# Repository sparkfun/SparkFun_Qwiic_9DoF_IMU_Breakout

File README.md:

SparkFun Qwiic 9DoF IMU  Breakout
========================================

[*SparkFun Qwiic 9DoF IMU  Breakout (15335)*](https://www.sparkfun.com/products/15335)

The SparkFun 9DoF IMU Breakout incorporates all the amazing features of Invensense's ICM-20948 into a Qwiic-enabled breakout board complete with a logic shifter and broken out GPIO pins for all your motion sensing needs. The ICM-20948 itself is an extremely low powered, I2C and SPI enabled 9-axis motion tracking device that is ideally suited for smartphones, tablets, wearable sensors, and IoT applications. Utilizing our handy Qwiic system, no soldering is required to connect it to the rest of your system. However, we still have broken out 0.1"-spaced pins in case you prefer to use a breadboard.

In addition to the 3-Axis Gyroscope with four selectable ranges, 3-Axis Accelerometer, again with four selectable ranges, and 3-axis magnetometer with an FSR to ±4900µT, the ICM-20948 also includes a Digital Motion Processor that offloads the computation of motion sensing algorithms from the detectors, allowing optimal performance of the sensors. We've also broken out all the ICM-20948 pin functionality to GPIO and labeled them I2C on the front, SPI on the back for ease of identification.

Repository Contents
-------------------

* **/Documentation** - Data sheets, additional product information
* **/Hardware** - Eagle design files (.brd, .sch)
* **/Production** - Production panel files (.brd)

Documentation
--------------
* **[Arduino Library](https://github.com/sparkfun/SparkFun_ICM-20948_ArduinoLibrary)** - Arduino library for the SparkFun Qwiic 9DoF IMU  Breakout.
* **[Python Package](https://github.com/sparkfun/Qwiic_9DoF_IMU_ICM20948_Py)** - Python Package (Qwiic_Py) for the SparkFun Qwiic 9DoF IMU  Breakout.
* **[Hookup Guide](https://learn.sparkfun.com/tutorials/sparkfun-9dof-imu-icm-20948-breakout-hookup-guide)** - Basic hookup guide for the SparkFun 9DoF IMU Breakout.
* **[SparkFun Fritzing repo](https://github.com/sparkfun/Fritzing_Parts)** - Fritzing diagrams for SparkFun products.

License Information
-------------------

This product is _**open source**_! 

Please review the LICENSE.md file for license information. 

If you have any questions or concerns on licensing, please contact techsupport@sparkfun.com.

Distributed as-is; no warranty is given.

- Your friends at SparkFun.

_<COLLABORATION CREDIT>_

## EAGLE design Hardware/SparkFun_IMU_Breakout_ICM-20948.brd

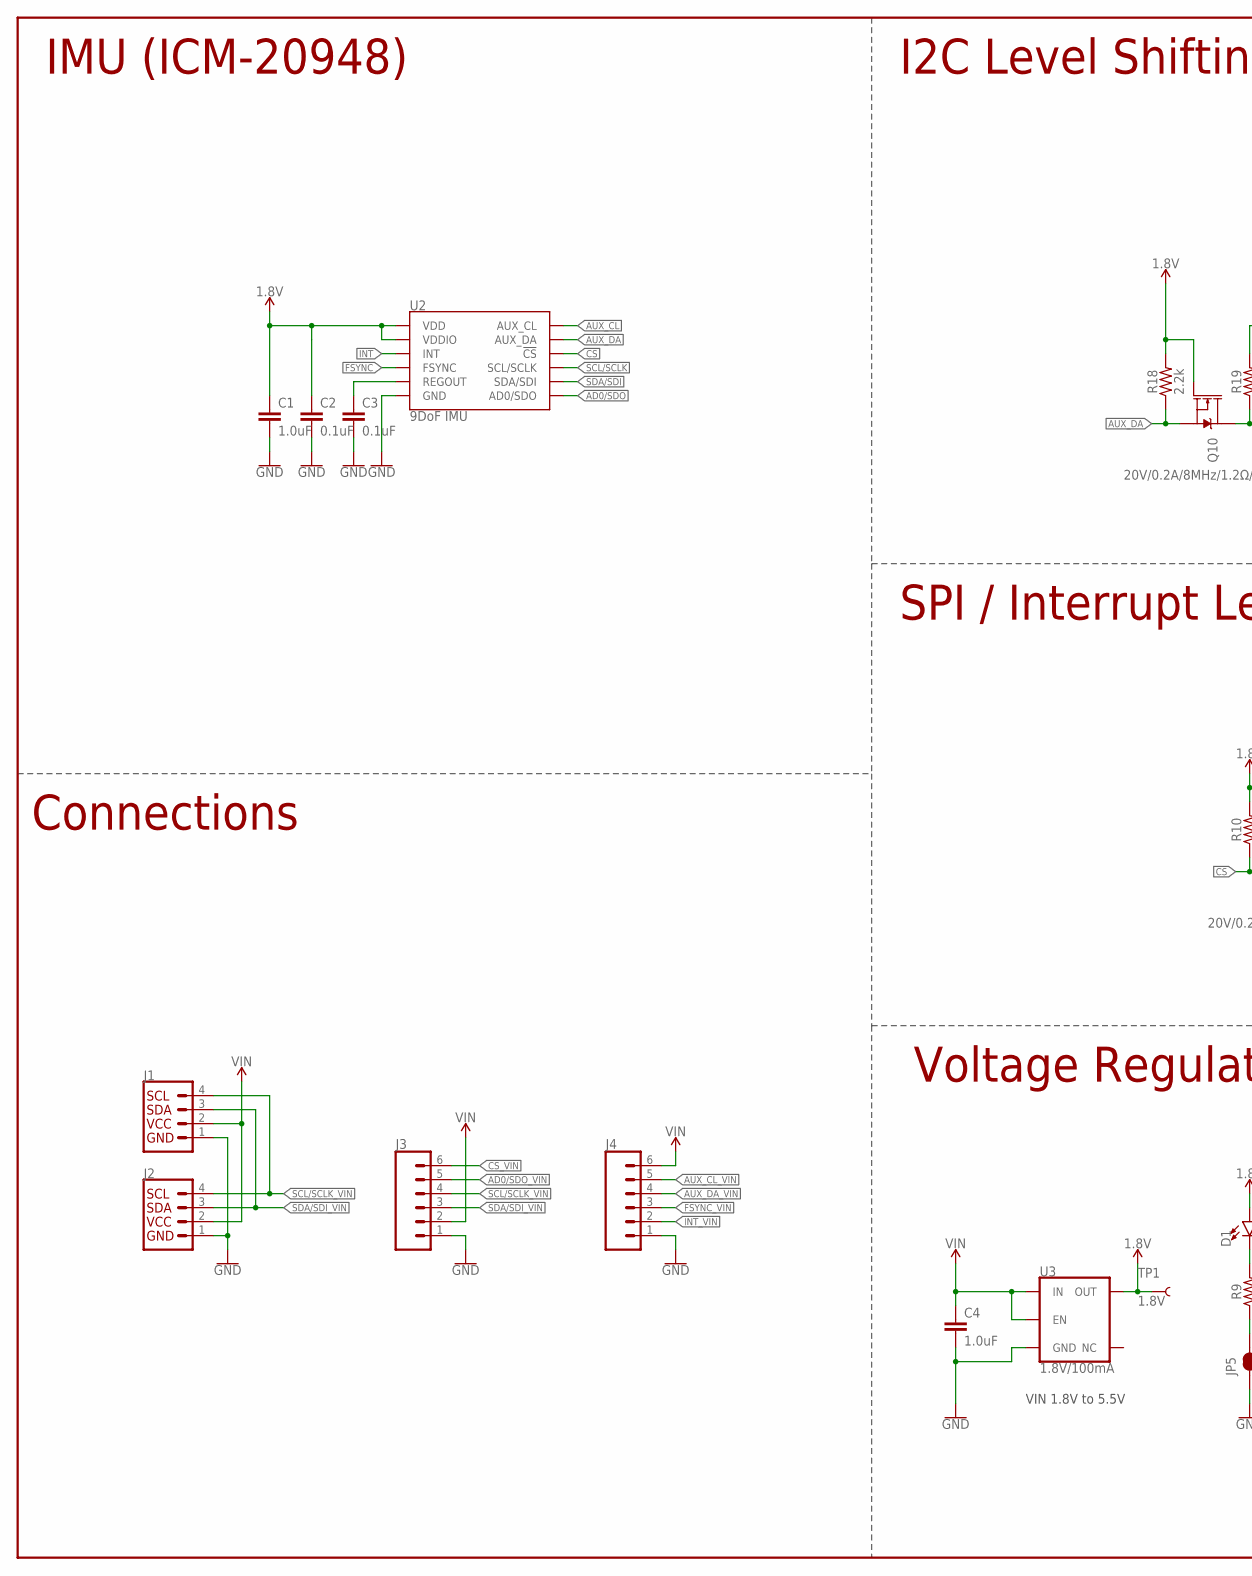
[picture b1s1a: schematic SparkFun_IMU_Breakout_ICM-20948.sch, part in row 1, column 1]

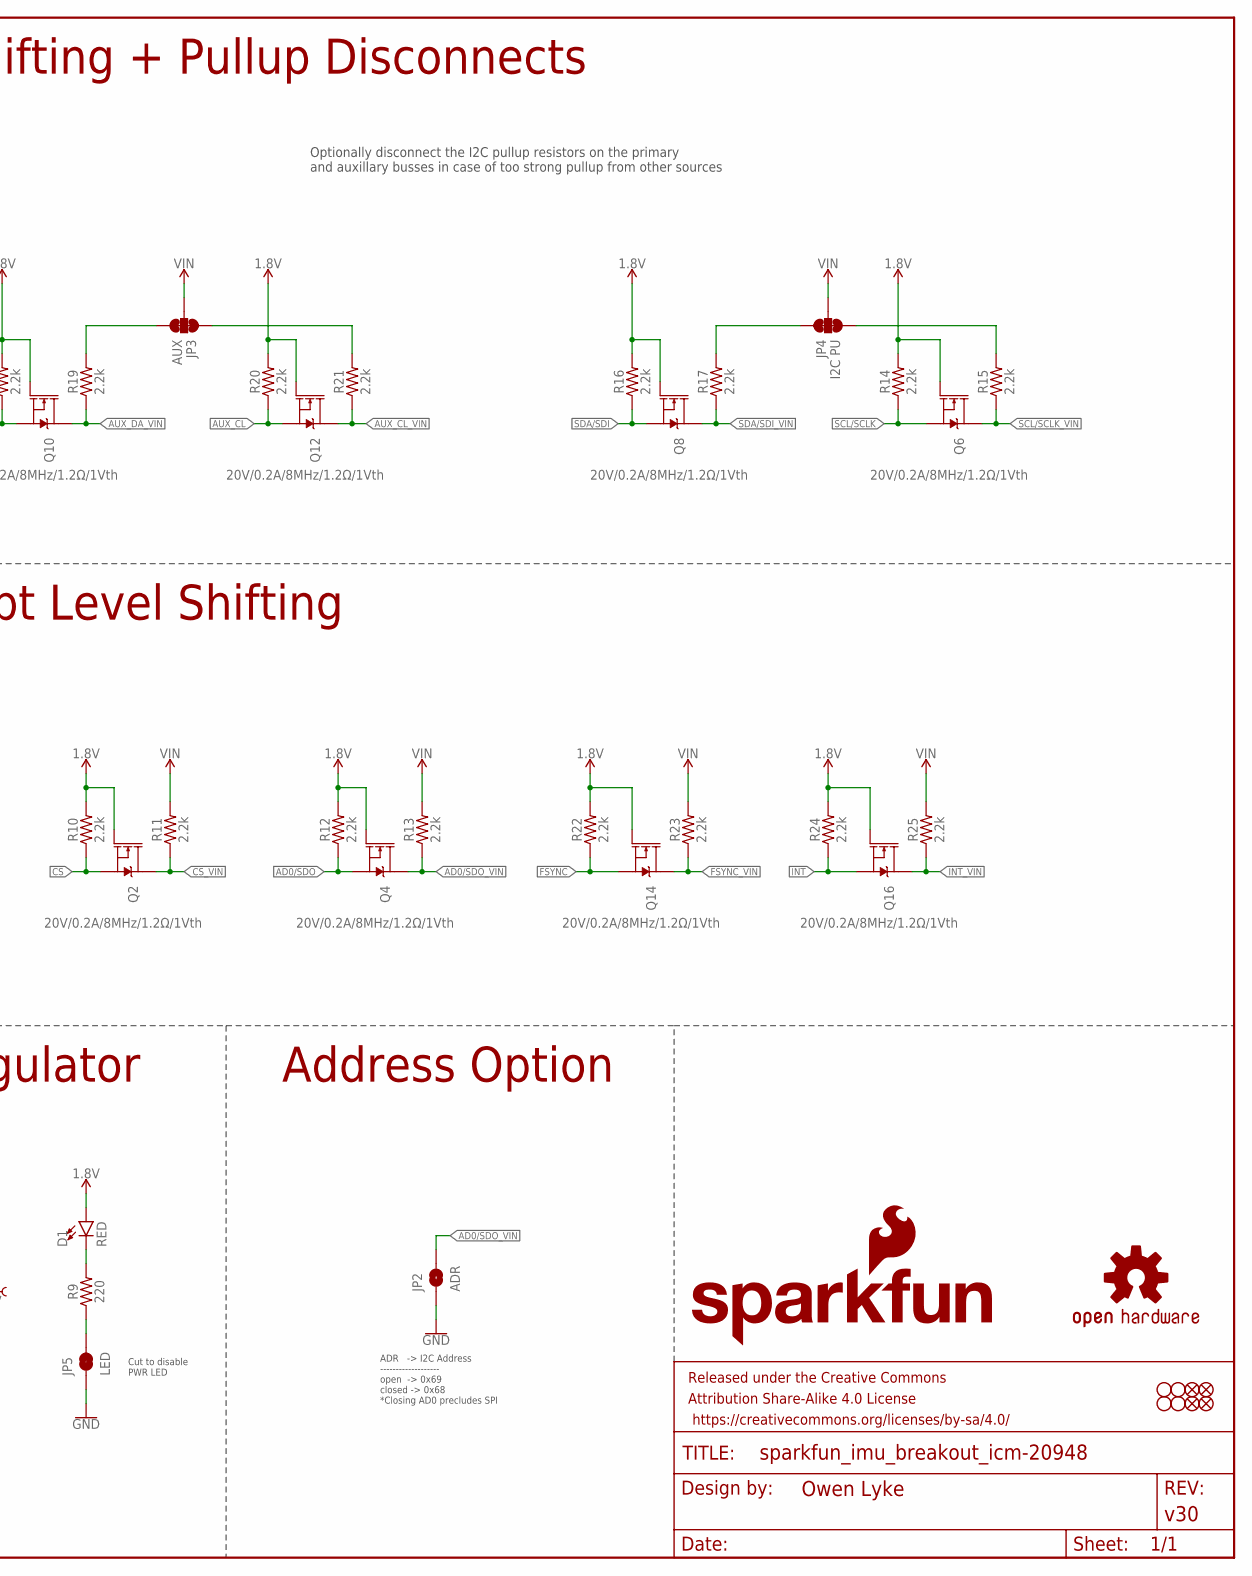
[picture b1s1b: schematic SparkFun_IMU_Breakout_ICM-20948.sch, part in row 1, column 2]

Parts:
C1, C4: 1.0uF; 0603
C2, C3: 0.1uF; 0603
D1: RED; LED-0603
FD1, FD2, FD3, FD4: FIDUCIAL1X2; FIDUCIAL-1X2
FRAME2: FRAME-LEDGER; CREATIVE_COMMONS
H1, H2, H3, H4: STAND-OFF
J1, J2: QWIIC_CONNECTORJS-1MM; JST04_1MM_RA
J3, J4: CONN_06NO_SILK_NO_POP; 1X06_NO_SILK
JP2: ADR; SMT-JUMPER_2_NO_SILK
JP3: AUX; SMT-JUMPER_3_2-NC_TRACE_SILK
JP4: I2C PU; SMT-JUMPER_3_2-NC_TRACE_SILK
JP5: LED; SMT-JUMPER_2_NC_TRACE_SILK
LOGO1: SFE_LOGO_NAME_FLAME.1_INCH; SFE_LOGO_NAME_FLAME_.1
LOGO2: OSHW-LOGOMINI; OSHW-LOGO-MINI
Q2, Q4, Q6, Q8, Q10, Q12, Q14, Q16: 20V/0.2A/8MHz/1.2Ω/1Vth; SOT-416FL
R9: 220; 0603
R10, R11, R12, R13, R14, R15, R16, R17, R18, R19, R20, R21, R22, R23, R24, R25: 2.2k; 0402-TIGHT
TP1: 1.8V; PAD.03X.03
U2: 9DoF IMU; QFN24-3X3
U3: 1.8V/100mA; SC70

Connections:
1.8V: C1.1, C2.1, D1.A, Q2.1 (G), Q4.1 (G), Q6.1 (G), Q8.1 (G), Q10.1 (G), Q12.1 (G), Q14.1 (G), Q16.1 (G), R10.2, R12.2, R14.2, R16.2, R18.2, R20.2, R22.2, R24.2, TP1.P$1, U2.8 (VDDIO), U2.13 (VDD), U3.5 (OUT)
!CS: Q2.2 (S), R10.1, U2.22 (!CS)
!CS!_VIN: J3.6, Q2.3 (D), R11.1
AD0/SDO: Q4.2 (S), R12.1, U2.9 (AD0/SDO)
AD0/SDO_VIN: J3.5, JP2.2, Q4.3 (D), R13.1
AUX_CL: Q12.2 (S), R20.1, U2.7 (AUX_CL)
AUX_CL_VIN: J4.5, Q12.3 (D), R21.1
AUX_DA: Q10.2 (S), R18.1, U2.21 (AUX_DA)
AUX_DA_VIN: J4.4, Q10.3 (D), R19.1
FSYNC: Q14.2 (S), R22.1, U2.11 (FSYNC)
FSYNC_VIN: J4.3, Q14.3 (D), R23.1
GND: C1.2, C2.2, C3.2, C4.2, J1.1, J2.1, J3.1, J4.1, JP2.1, JP5.1, U2.18 (GND), U2.20 (GND), U3.2 (GND)
INT: Q16.2 (S), R24.1, U2.12 (INT)
INT_VIN: J4.2, Q16.3 (D), R25.1
unnamed: C3.1, U2.10 (REGOUT)
unnamed: JP4.3, R15.2
unnamed: JP4.1, R17.2
unnamed: JP3.1, R21.2
unnamed: JP3.3, R19.2
unnamed: D1.C, R9.2
unnamed: JP5.2, R9.1
SCL/SCLK: Q6.2 (S), R14.1, U2.23 (SCL/SCLK)
SCL/SCLK_VIN: J1.4, J2.4, J3.4, Q6.3 (D), R15.1
SDA/SDI: Q8.2 (S), R16.1, U2.24 (SDA/SDI)
SDA/SDI_VIN: J1.3, J2.3, J3.3, Q8.3 (D), R17.1
VIN: C4.1, J1.2, J2.2, J3.2, J4.6, JP3.2, JP4.2, R11.2, R13.2, R23.2, R25.2, U3.1 (IN), U3.3 (EN)

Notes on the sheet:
VIN 1.8V to 5.5V
IMU (ICM-20948)
I2C Level Shifting + Pullup Disconnects
Connections
Voltage Regulator
SPI / Interrupt Level Shifting
ADR -> I2C Address ------------------- open -> 0x69 closed -> 0x68 *Closing AD0 precludes SPI
Optionally disconnect the I2C pullup resistors on the primary and auxillary busses in case of too strong pullup from other sources
Cut to disable PWR LED
Address Option

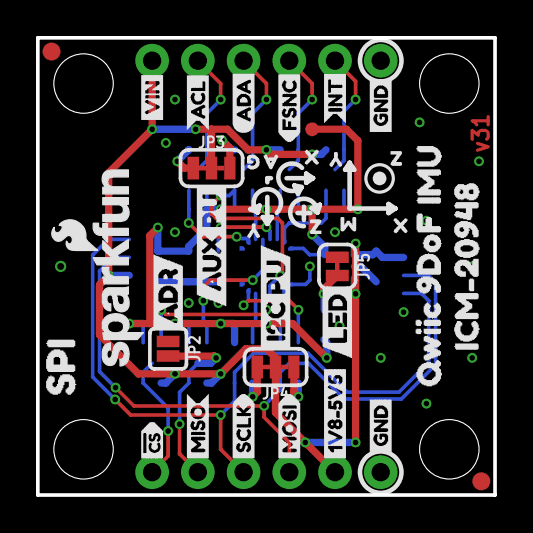
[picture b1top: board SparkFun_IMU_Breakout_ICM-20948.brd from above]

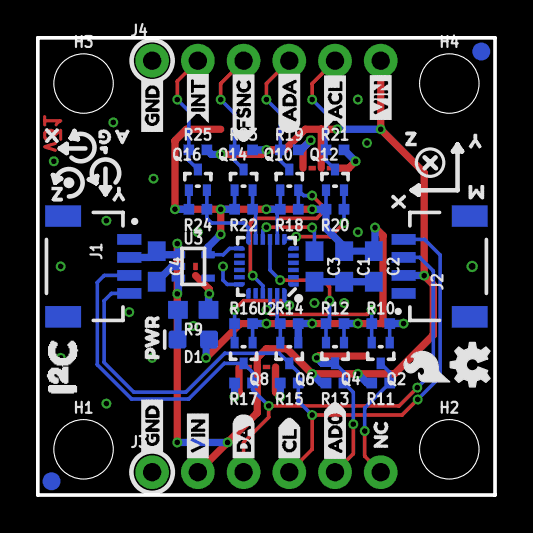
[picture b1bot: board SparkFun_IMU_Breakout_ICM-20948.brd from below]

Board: 2 copper layers, 25.4 x 25.4 mm, 104 parts (68 on the bottom side), 26 nets.

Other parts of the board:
U$1, U$2, U$22, U$24: GND4
U$3: PWR0
U$4, U$21: INT3
U$5, U$20: FSNC2
U$6, U$19: ACL1
U$7, U$18: ADA0
U$8: MISO13
U$9: MOSI14
U$10: SCLK15
U$11: #CS16
U$12: 1V8#5V57
U$13, U$30, U$44: VIN5
U$14: NC17
U$15: CL4
U$16: DA2
U$17: AD012
U$23: ADR2
U$25: I2C_PU21
U$26: SPI19
U$27: AUX_PU24
U$28: SFE_LOGO_FLAME_.1
U$29: LED23
U$31: ICM#2094820
U$34, U$40, U$50, U$57: X0
U$35, U$41, U$51, U$58: Y1
U$36, U$42, U$52, U$59: Z2
U$37, U$60: G5
U$38, U$61: A4
U$39, U$49: M3
U$43: QWIIC_9DOF_IMU_0
U$45: I#C1

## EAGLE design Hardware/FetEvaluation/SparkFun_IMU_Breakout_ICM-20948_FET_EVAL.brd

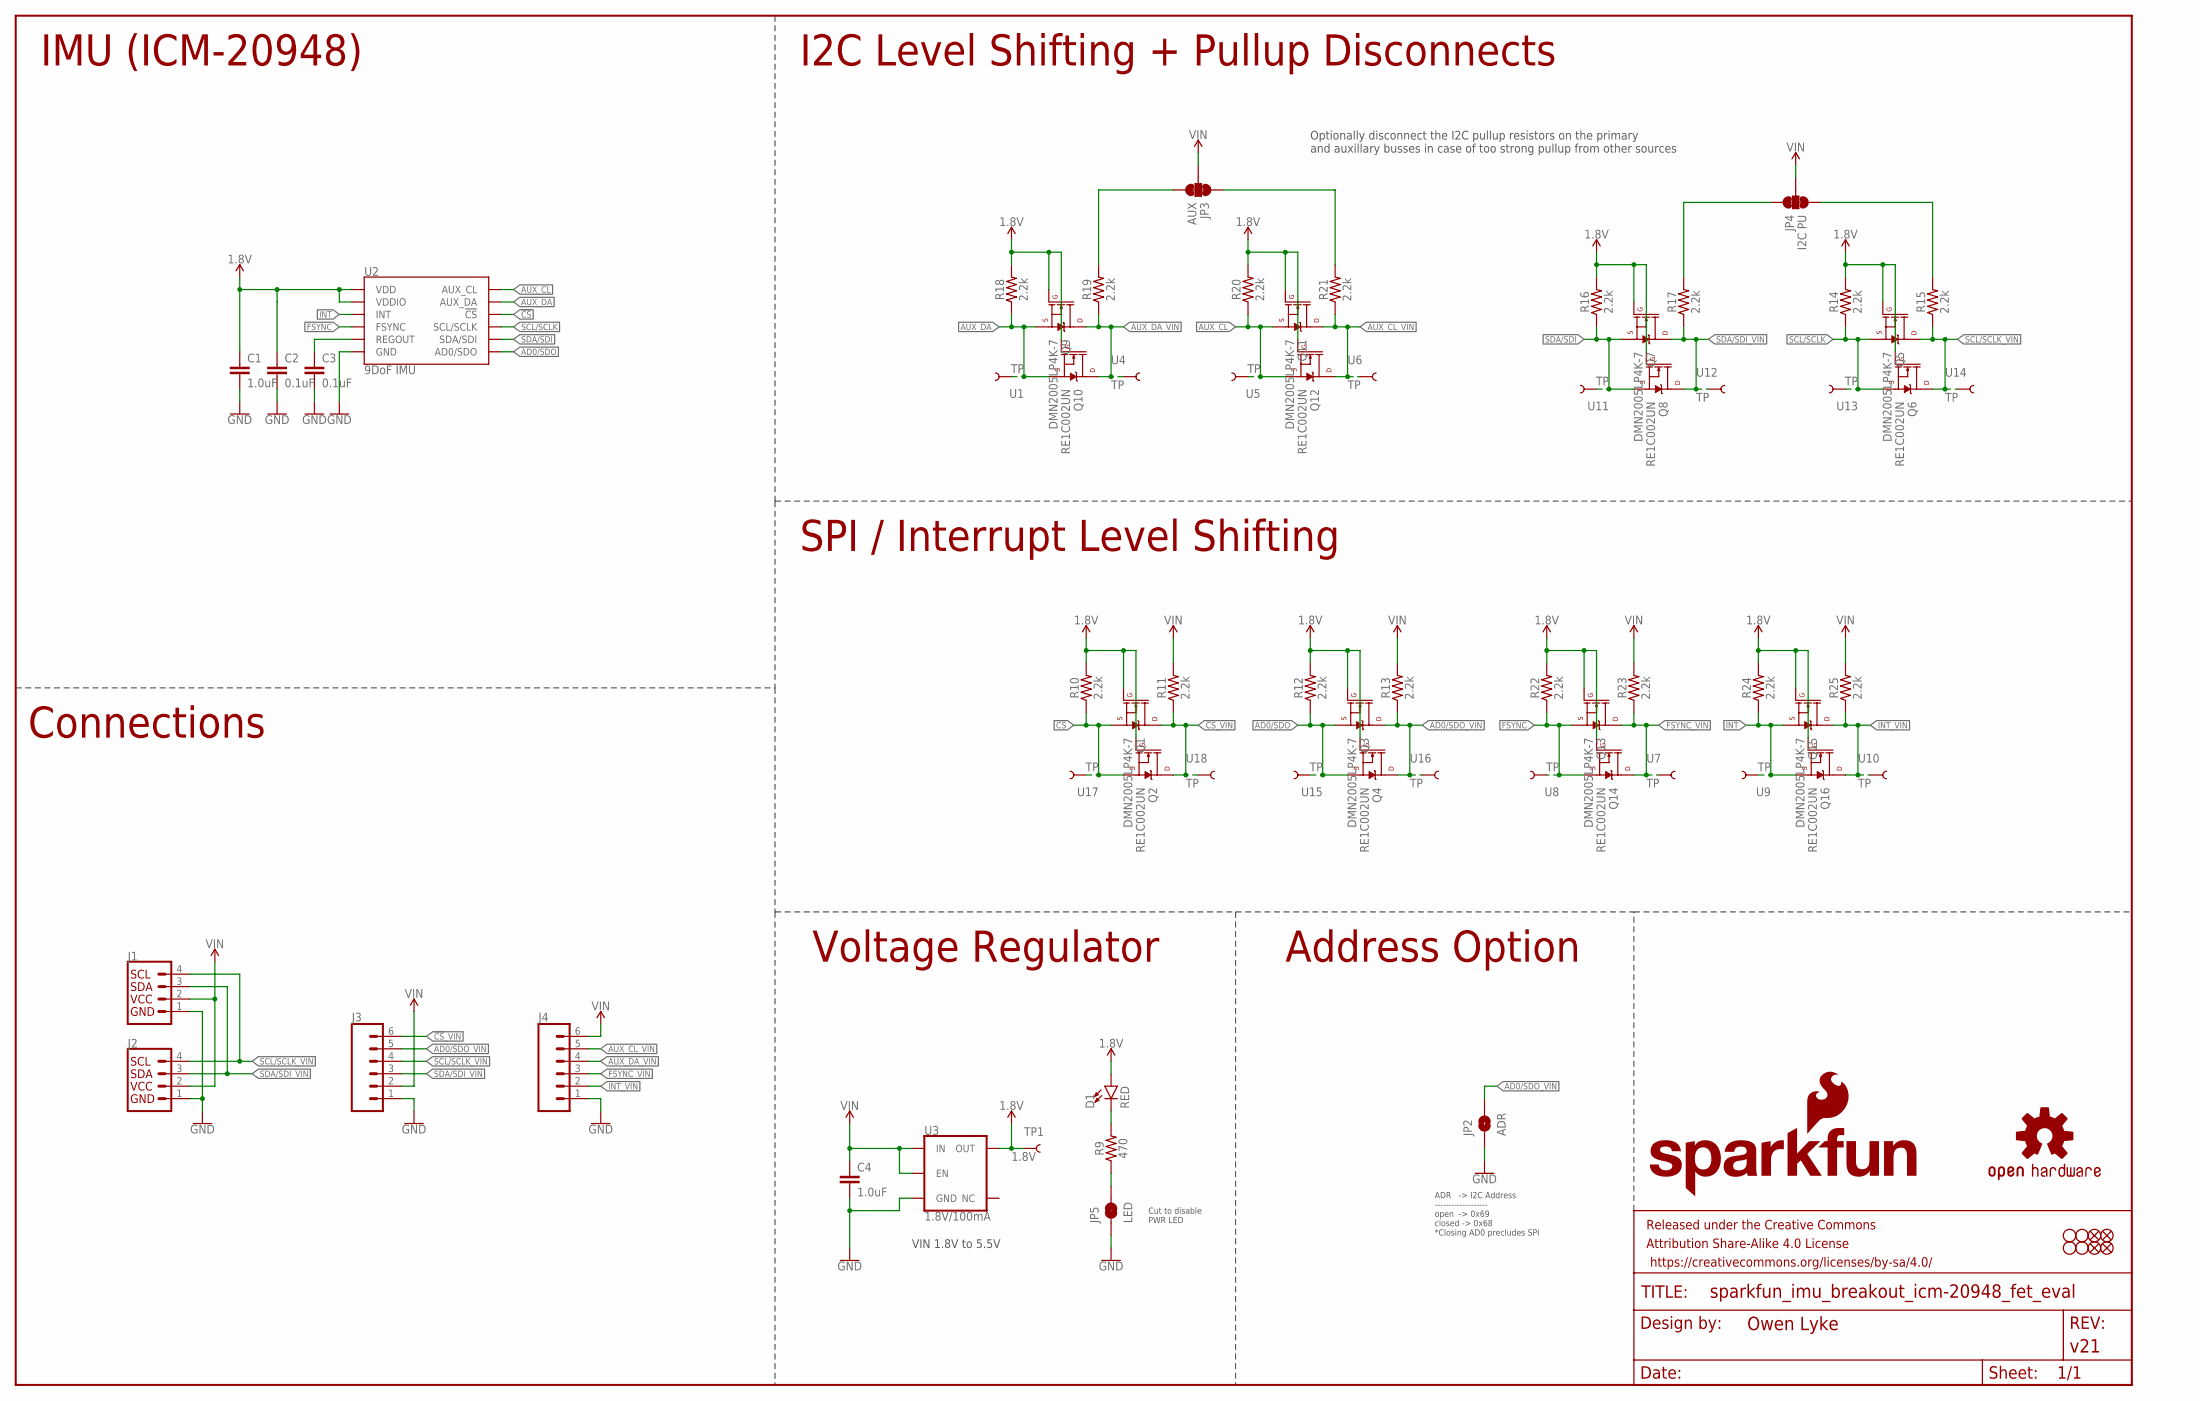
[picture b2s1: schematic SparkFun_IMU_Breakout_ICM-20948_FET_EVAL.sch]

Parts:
C1, C4: 1.0uF; 0603
C2, C3: 0.1uF; 0603
D1: RED; LED-0603
FD1, FD2, FD3, FD4: FIDUCIAL1X2; FIDUCIAL-1X2
FRAME2: FRAME-LEDGER; CREATIVE_COMMONS
H1, H2, H3, H4: STAND-OFF
J1, J2: QWIIC_CONNECTORJS-1MM; JST04_1MM_RA
J3, J4: CONN_06NO_SILK_NO_POP; 1X06_NO_SILK
JP2: ADR; SMT-JUMPER_2_NO_SILK
JP3: AUX; SMT-JUMPER_3_2-NC_TRACE_SILK
JP4: I2C PU; SMT-JUMPER_3_2-NC_TRACE_SILK
JP5: LED; SMT-JUMPER_2_NC_TRACE_SILK
LOGO1: SFE_LOGO_NAME_FLAME.1_INCH; SFE_LOGO_NAME_FLAME_.1
LOGO2: OSHW-LOGOMINI; OSHW-LOGO-MINI
Q1, Q3, Q5, Q7, Q9, Q11, Q13, Q15: DMN2005LP4K-7; AP02001
Q2, Q4, Q6, Q8, Q10, Q12, Q14, Q16: RE1C002UN; SOT-416FL
R9: 470; 0603
R10, R11, R12, R13, R14, R15, R16, R17, R18, R19, R20, R21, R22, R23, R24, R25: 2.2k; 0402-TIGHT
TP1: 1.8V; PAD.03X.03
U1, U4, U5, U6, U7, U8, U9, U10, U11, U12, U13, U14, U15, U16, U17, U18: TP; MINI_TEST_POINT
U2: 9DoF IMU; QFN24-3X3
U3: 1.8V/100mA; SC70

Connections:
1.8V: C1.1, C2.1, D1.A, Q1.G, Q2.1 (G), Q3.G, Q4.1 (G), Q5.G, Q6.1 (G), Q7.G, Q8.1 (G), Q9.G, Q10.1 (G), Q11.G, Q12.1 (G), Q13.G, Q14.1 (G), Q15.G, Q16.1 (G), R10.2, R12.2, R14.2, R16.2, R18.2, R20.2, R22.2, R24.2, TP1.P$1, U2.8 (VDDIO), U2.13 (VDD), U3.5 (OUT)
!CS: Q1.S, Q2.2 (S), R10.1, U2.22 (!CS), U17.P$1
!CS!_VIN: J3.6, Q1.D, Q2.3 (D), R11.1, U18.P$1
AD0/SDO: Q3.S, Q4.2 (S), R12.1, U2.9 (AD0/SDO), U15.P$1
AD0/SDO_VIN: J3.5, JP2.2, Q3.D, Q4.3 (D), R13.1, U16.P$1
AUX_CL: Q11.S, Q12.2 (S), R20.1, U2.7 (AUX_CL), U5.P$1
AUX_CL_VIN: J4.5, Q11.D, Q12.3 (D), R21.1, U6.P$1
AUX_DA: Q9.S, Q10.2 (S), R18.1, U1.P$1, U2.21 (AUX_DA)
AUX_DA_VIN: J4.4, Q9.D, Q10.3 (D), R19.1, U4.P$1
FSYNC: Q13.S, Q14.2 (S), R22.1, U2.11 (FSYNC), U8.P$1
FSYNC_VIN: J4.3, Q13.D, Q14.3 (D), R23.1, U7.P$1
GND: C1.2, C2.2, C3.2, C4.2, J1.1, J2.1, J3.1, J4.1, JP2.1, JP5.1, U2.18 (GND), U2.20 (GND), U3.2 (GND)
INT: Q15.S, Q16.2 (S), R24.1, U2.12 (INT), U9.P$1
INT_VIN: J4.2, Q15.D, Q16.3 (D), R25.1, U10.P$1
unnamed: C3.1, U2.10 (REGOUT)
unnamed: JP4.3, R15.2
unnamed: JP4.1, R17.2
unnamed: JP3.1, R21.2
unnamed: JP3.3, R19.2
unnamed: D1.C, R9.2
unnamed: JP5.2, R9.1
SCL/SCLK: Q5.S, Q6.2 (S), R14.1, U2.23 (SCL/SCLK), U13.P$1
SCL/SCLK_VIN: J1.4, J2.4, J3.4, Q5.D, Q6.3 (D), R15.1, U14.P$1
SDA/SDI: Q7.S, Q8.2 (S), R16.1, U2.24 (SDA/SDI), U11.P$1
SDA/SDI_VIN: J1.3, J2.3, J3.3, Q7.D, Q8.3 (D), R17.1, U12.P$1
VIN: C4.1, J1.2, J2.2, J3.2, J4.6, JP3.2, JP4.2, R11.2, R13.2, R23.2, R25.2, U3.1 (IN), U3.3 (EN)

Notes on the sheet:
VIN 1.8V to 5.5V
IMU (ICM-20948)
I2C Level Shifting + Pullup Disconnects
Connections
Voltage Regulator
SPI / Interrupt Level Shifting
ADR -> I2C Address ------------------- open -> 0x69 closed -> 0x68 *Closing AD0 precludes SPI
Optionally disconnect the I2C pullup resistors on the primary and auxillary busses in case of too strong pullup from other sources
Cut to disable PWR LED
Address Option

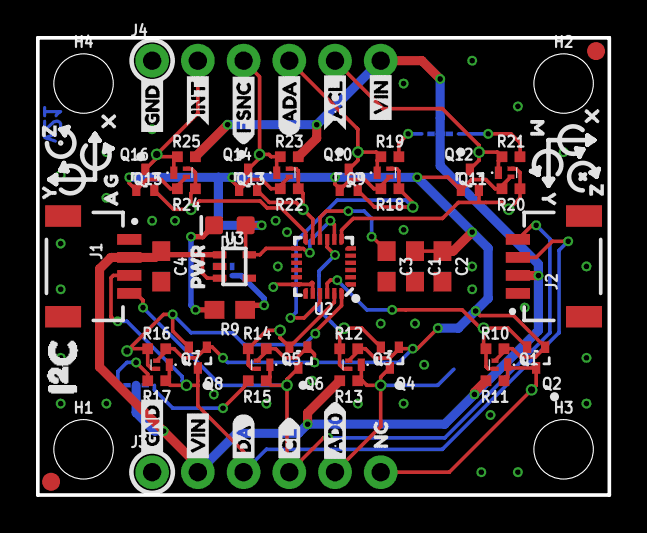
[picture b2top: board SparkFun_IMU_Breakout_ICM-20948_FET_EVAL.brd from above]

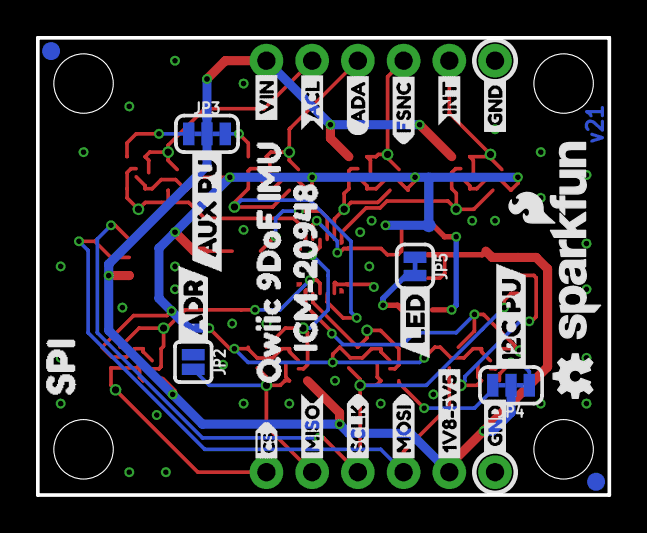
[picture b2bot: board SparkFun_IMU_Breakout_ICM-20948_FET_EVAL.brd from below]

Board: 2 copper layers, 31.8 x 25.4 mm, 118 parts (28 on the bottom side), 26 nets.

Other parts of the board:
U$1, U$2, U$22, U$24: GND4
U$3: PWR0
U$4, U$21: INT3
U$5, U$20: FSNC2
U$6, U$19: ACL1
U$7, U$18: ADA0
U$8: MISO13
U$9: MOSI14
U$10: SCLK15
U$11: #CS16
U$12: 1V8#5V57
U$13, U$30, U$44: VIN5
U$14: NC17
U$15: CL4
U$16: DA2
U$17: AD012
U$23: ADR2
U$25: I2C_PU21
U$26: SPI19
U$27: AUX_PU24
U$29: LED23
U$31: ICM#2094820
U$34, U$40: X0
U$35, U$41: Y1
U$36, U$42: Z2
U$37: G5
U$38: A4
U$39: M3
U$43: QWIIC_9DOF_IMU_0
U$45: I#C1

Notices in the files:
parts and their libraries:
SparkFun-Capacitors: Licensing: Creative Commons ShareAlike 4.0 International - https://creativecommons.org/licenses/by-sa/4.0
SparkFun-Aesthetics: Released under the Creative Commons Attribution Share-Alike 4.0 License
SparkFun-Aesthetics: https://creativecommons.org/licenses/by-sa/4.0
